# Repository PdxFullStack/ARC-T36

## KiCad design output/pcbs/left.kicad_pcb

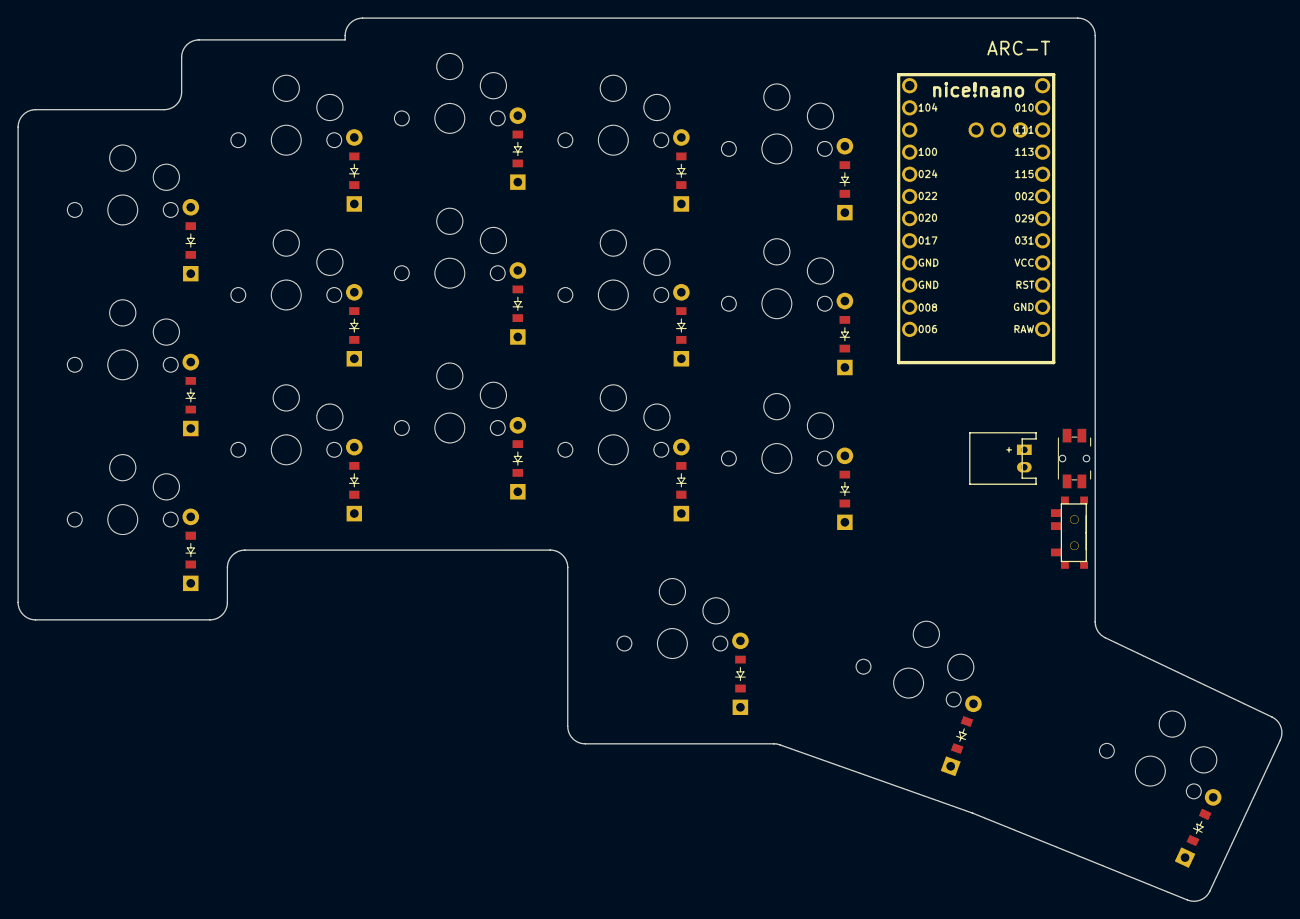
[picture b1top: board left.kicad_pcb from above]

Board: 2 copper layers, 144.9 x 101.3 mm, 40 parts (0 on the bottom side), 34 nets, no tracks yet.

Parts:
B1: Panasonic_EVQPUL_EVQPUC
D1, D2, D3, D4, D5, D6, D7, D8, D9, D10, D11, D12, D13, D14, D15, D16, D17, D18: ComboDiode
JST1: JST_PH_S2B-PH-K_02x2.00mm_Angled
MCU1: nice_nano
S1, S2, S3, S4, S5, S6, S7, S8, S9, S10, S11, S12, S13, S14, S15, S16, S17, S18: PG1350
T1: SPDT_C128955

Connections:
GND: B1.1, JST1.2, MCU1.3, MCU1.4, MCU1.23
P002: D3.1, D6.1, D9.1, D12.1, D15.1, MCU1.18
P009: MCU1.13, S17.1
P010: MCU1.14, S18.1
P011: MCU1.10, S13.1, S14.1, S15.1
P017: D16.1, D17.1, D18.1, MCU1.5
P020: MCU1.6, S1.1, S2.1, S3.1
P022: MCU1.7, S4.1, S5.1, S6.1
P024: MCU1.8, S7.1, S8.1, S9.1
P100: MCU1.9, S10.1, S11.1, S12.1
P111: MCU1.15, S16.1
P113: D1.1, D4.1, D7.1, D10.1, D13.1, MCU1.16
P115: D2.1, D5.1, D8.1, D11.1, D14.1, MCU1.17
RAW: MCU1.24, T1.2
RST: B1.2, MCU1.22
home_cluster: D17.2, S17.2
index_bottom: D10.2, S10.2
index_home: D11.2, S11.2
index_top: D12.2, S12.2
inner_bottom: D13.2, S13.2
inner_cluster: D16.2, S16.2
inner_home: D14.2, S14.2
inner_top: D15.2, S15.2
middle_bottom: D7.2, S7.2
middle_home: D8.2, S8.2
middle_top: D9.2, S9.2
outer_cluster: D18.2, S18.2
pinky_bottom: D1.2, S1.2
pinky_home: D2.2, S2.2
pinky_top: D3.2, S3.2
pos: JST1.1, T1.1
ring_bottom: D4.2, S4.2
ring_home: D5.2, S5.2
ring_top: D6.2, S6.2

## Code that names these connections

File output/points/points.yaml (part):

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        autobind: 10
        skip: false
        asym: both
        colrow: pinky_bottom
        name: matrix_pinky_bottom
        column_net: P020
        row_net: P113
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        autobind: 10
        skip: false
        asym: both
        colrow: pinky_home
        name: matrix_pinky_home
        column_net: P020
        row_net: P115
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        autobind: 10
        skip: false
        asym: both
        colrow: pinky_top
        name: matrix_pinky_top
        column_net: P020
        row_net: P002
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
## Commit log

2024-10-16 init
2024-10-16 adds footprints
2024-10-16 tiding up in the upper portion of border
2024-10-16 v1 design
